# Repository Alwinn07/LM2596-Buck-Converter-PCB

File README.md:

# LM2596-Buck-Converter-PCB
A KiCad-based PCB design of a 12V to 5V DC-DC buck converter using the LM2596S-5 switching regulator. The project delivers a stable 5V output with input/output filtering, Schottky freewheeling diode, LED load testing, and complete design files including schematic, PCB layout, BOM, and manufacturing-ready Gerber files

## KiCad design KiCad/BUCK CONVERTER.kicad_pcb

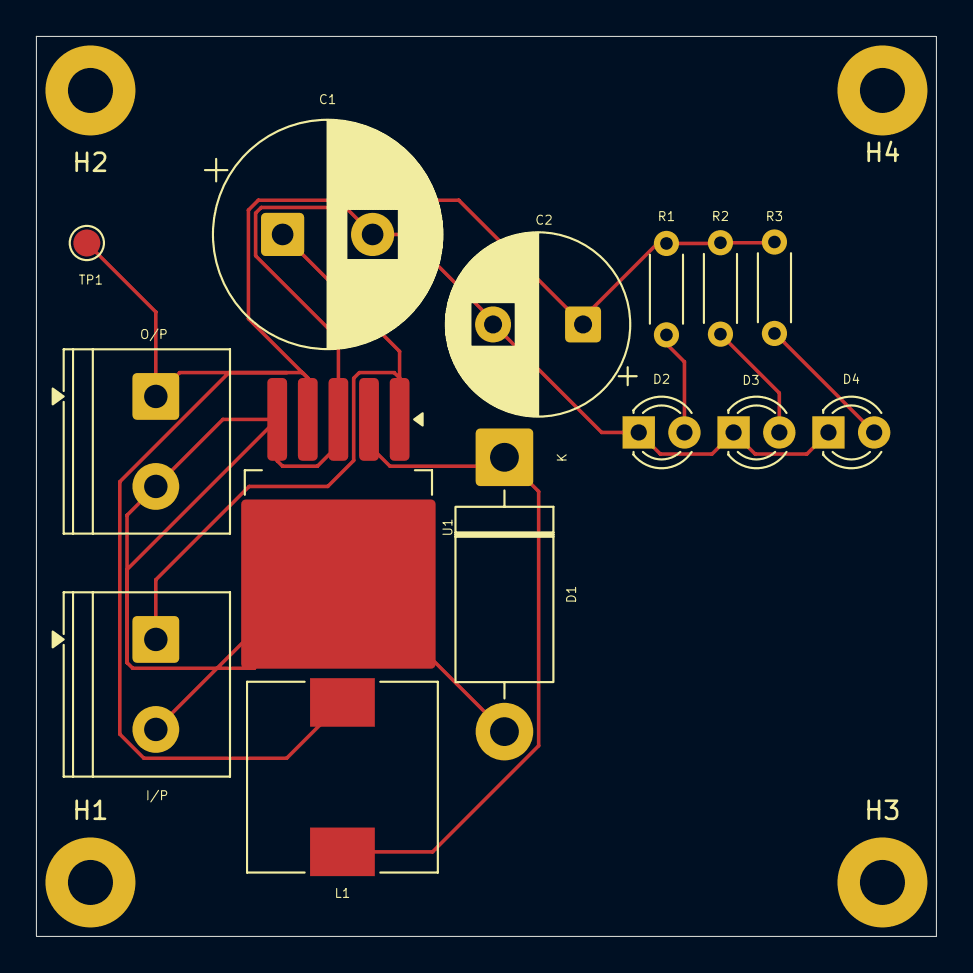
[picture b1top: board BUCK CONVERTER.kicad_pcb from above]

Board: 2 copper layers, 50.0 x 50.0 mm, 18 parts (0 on the bottom side), 7 nets.

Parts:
C1: 680 uF; CP_Radial_D12.5mm_P5.00mm
C2: 220 uF; CP_Radial_D10.0mm_P5.00mm
D1: SS34; D_DO-201AD_P15.24mm_Horizontal
D2, D3, D4: LED; LED_D3.0mm
H1, H2, H3, H4: MountingHole; MountingHole_2.5mm_Pad
I/P: 12 v; TerminalBlock_Phoenix_PT-1,5-2-5.0-H_1x02_P5.00mm_Horizontal
L1: 33 uH; L_10.4x10.4_H4.8
O/P: 5 v; TerminalBlock_Phoenix_PT-1,5-2-5.0-H_1x02_P5.00mm_Horizontal
R1, R2, R3: 330; R_Axial_DIN0204_L3.6mm_D1.6mm_P5.08mm_Horizontal
TP1: TestPoint; TestPoint_Pad_D1.5mm
U1: LM2596S-5; TO-263-5_TabPin3

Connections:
GND: C1.2, C2.2, D1.2 (A), D2.1 (K), D3.1 (K), D4.1 (K), I/P.2, O/P.2, U1.3 (GND), U1.5 (~ON/OFF)
unnamed: D1.1 (K), L1.1, U1.2 (OUT)
unnamed: D2.2 (A), R1.2
unnamed: D3.2 (A), R2.2
unnamed: D4.2 (A), R3.2
unnamed: C1.1, I/P.1, U1.1 (VIN)
unnamed: C2.1, L1.2, O/P.1, R1.1, R2.1, R3.1, TP1.1 (1_1), U1.4 (FB)
